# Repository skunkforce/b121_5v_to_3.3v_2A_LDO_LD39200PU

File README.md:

# edgy_board number b121
This design is part of the [edgy board project](https://github.com/skunkforce/edgy_boards).

# getting started
This repository uses submodules. After cloning use the command 

```$ git submodule update --init --recursive```

to pull the submodules before opening the project with kicad. 

# Tests
Tests can be found in [TESTS.md](TESTS.md)

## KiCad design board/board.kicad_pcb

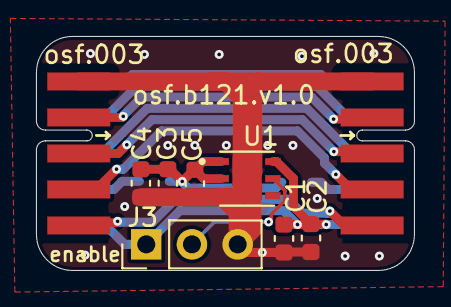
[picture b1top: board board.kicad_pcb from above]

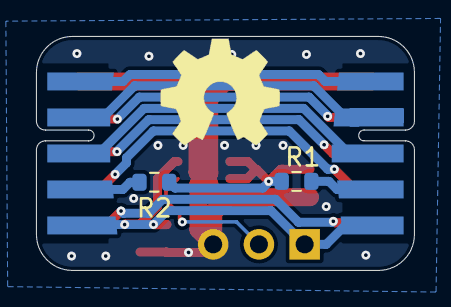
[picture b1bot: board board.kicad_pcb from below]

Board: 2 copper layers, 21.0 x 13.0 mm, 12 parts (3 on the bottom side), 13 nets.

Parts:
C1, C5: 1uF; C_0603_1608Metric
C2, C3, C4: 10uF; C_0603_1608Metric
J1: 003_power; on_edge_2x05_device
J2: 003_power; on_edge_2x05_host
J3: Conn_01x03_Male; PinHeader_1x03_P2.54mm_Vertical
LOGO1: Logo_Open_Hardware_Small; OSHW-Symbol_6.7x6mm_SilkScreen
R1, R2: 0R; R_0603_1608Metric
U1: LD39200PU33R; SON95P300X300X100-7N

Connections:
/ldo/3.3v: C3.1, C4.1, C5.1, R1.2, R2.1, U1.1 (OUT), U1.2 (SENSE)
/ldo/5v: C1.1, C2.1, J1.10 (5V), J2.10 (5V), J3.1, U1.6 (IN)
/ldo/EN: J3.2, U1.5 (EN)
/ldo/GND: C1.2, C2.2, C3.2, C4.2, C5.2, J1.1 (GND), J2.1 (GND), J3.3, U1.3 (GND), U1.7 (EXP)
unnamed: J1.2 (GND), J2.2 (GND)
unnamed: J1.3 (GND), J2.3 (GND)
unnamed: J1.4 (GND), J2.4 (GND)
unnamed: J1.5 (GND), J2.5 (GND)
unnamed: J1.6 (1.2V), J2.6 (1.2V)
unnamed: J1.7 (1.8V), J2.7 (1.8V)
unnamed: J1.8 (2.5V), J2.8 (2.5V)
unnamed: J1.9 (3.3V), R1.1
unnamed: J2.9 (3.3V), R2.2

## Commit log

2023-03-30 initial
